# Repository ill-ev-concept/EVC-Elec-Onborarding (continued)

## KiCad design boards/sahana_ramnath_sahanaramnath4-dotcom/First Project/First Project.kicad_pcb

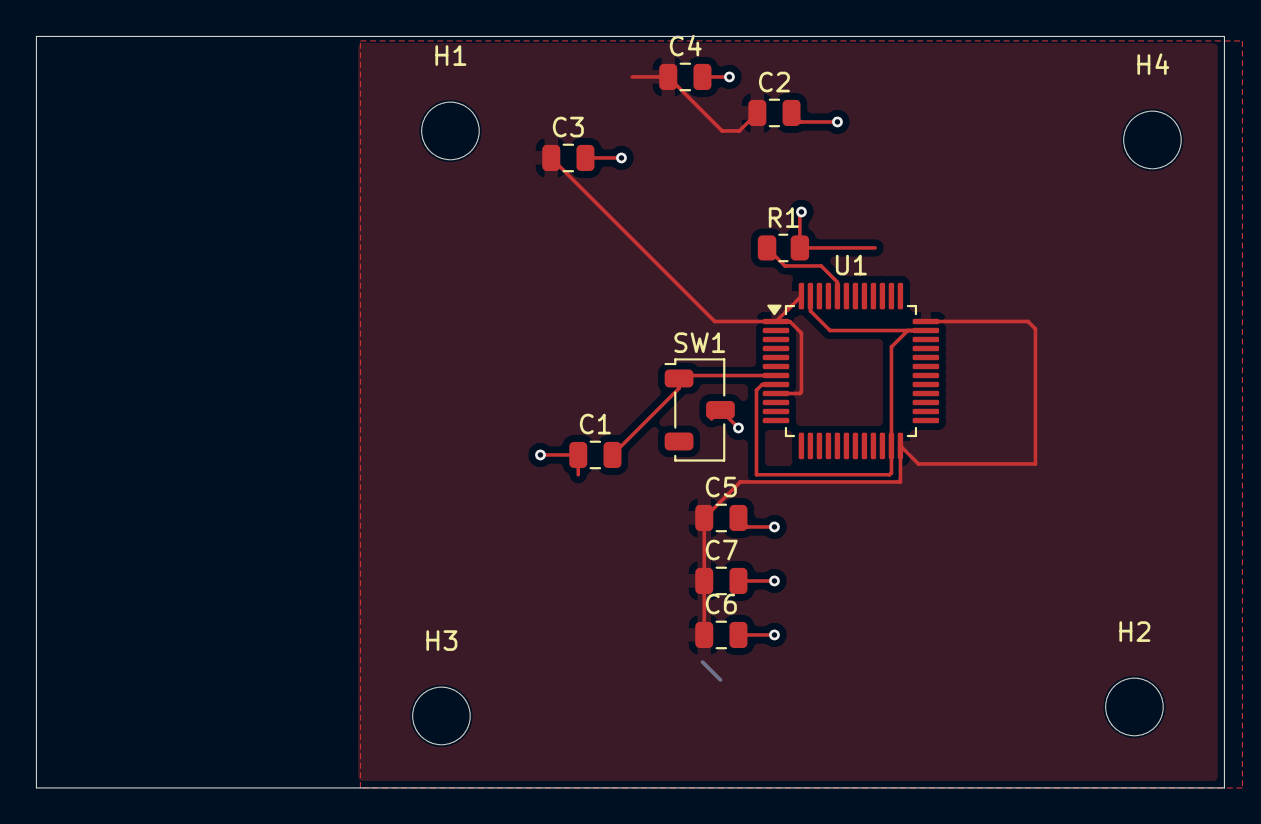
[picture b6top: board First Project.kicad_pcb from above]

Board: 2 copper layers, 66.0 x 41.8 mm, 14 parts (0 on the bottom side), 5 nets.

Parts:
C1: 100nF; C_0805_2012Metric
C2, C3, C6: 100 nF; C_0805_2012Metric
C4, C5: 100 nf; C_0805_2012Metric
C7: 4.7 microFarads; C_0805_2012Metric
H1, H2, H3, H4: MountingHole; MountingHole_3.2mm_M3
R1: 10K ohms; R_0805_2012Metric
SW1: SW_Push; Nidec_Copal_CAS-120A
U1: STM32F103C8Tx; LQFP-48_7x7mm_P0.5mm

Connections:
+3.3V: C2.1, C3.1, C4.1, C5.1, C6.1, C7.1, U1.1 (VBAT), U1.9 (VDDA), U1.24 (VDD), U1.36 (VDD), U1.48 (VDD)
BOOTOO: R1.1, U1.44 (BOOT0)
GND: C1.1, C2.2, C3.2, C4.2, C5.2, C6.2, C7.2, R1.2, SW1.2
NRST: C1.2, SW1.1, U1.7 (NRST)
unnamed: U1.8 (VSSA), U1.23 (VSS), U1.35 (VSS), U1.47 (VSS)

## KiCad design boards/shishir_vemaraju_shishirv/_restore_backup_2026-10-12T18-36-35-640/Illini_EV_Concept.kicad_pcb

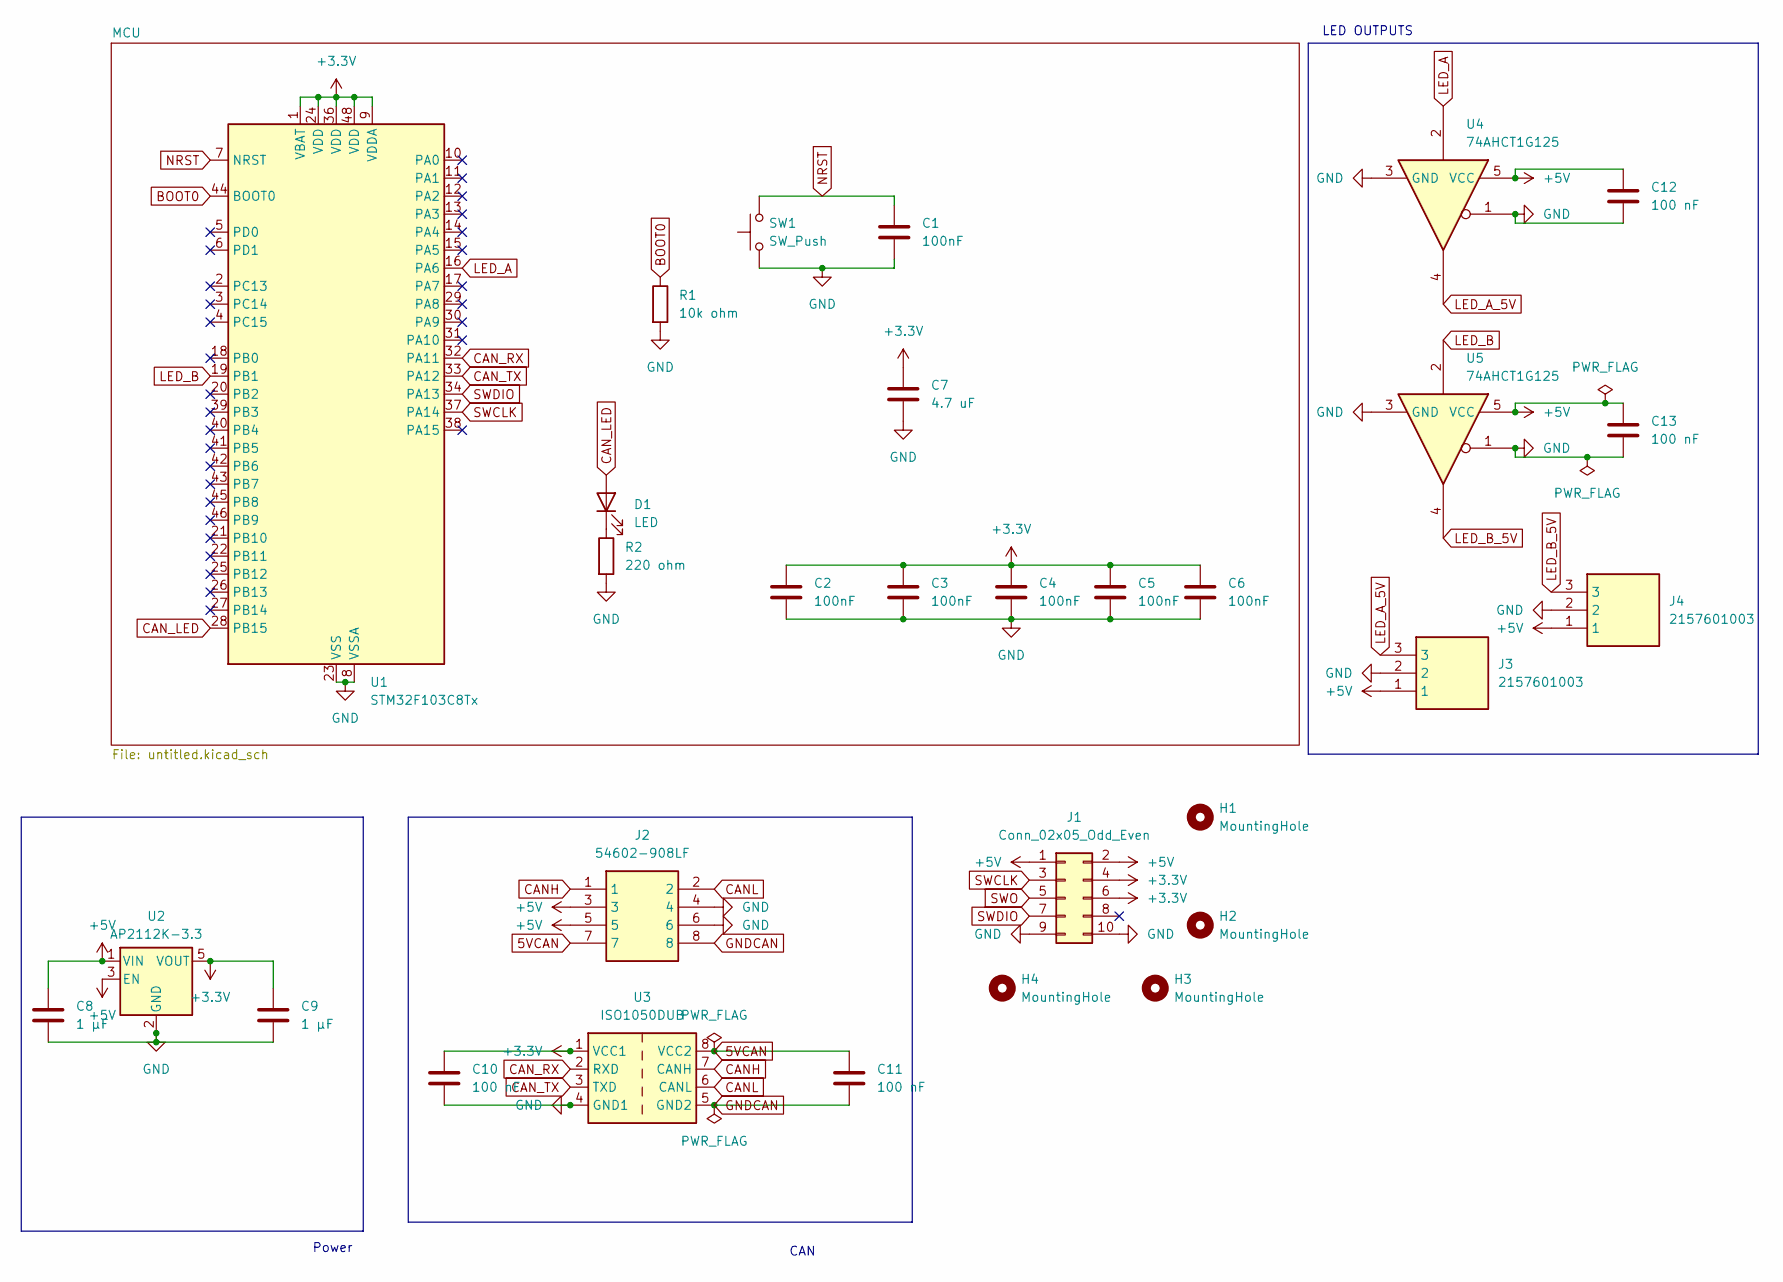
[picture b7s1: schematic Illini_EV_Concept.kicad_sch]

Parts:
C1, C2, C3, C4, C5, C6: 100nF; C_0603_1608Metric
C7: 4.7 uF; C_0603_1608Metric
C8, C9: 1 μF; C_0603_1608Metric
C10, C11, C12, C13: 100 nF; C_0603_1608Metric
D1: LED; LED_0603_1608Metric
H1, H2, H3, H4: MountingHole; MountingHole_4.3mm_M4
J1: Conn_02x05_Odd_Even; PinHeader_2x05_P2.54mm_Vertical
J2: 54602-908LF; 54602908LF; Manufacturer_Part_Number 54602-908LF
J3, J4: 2157601003; 215760YY03; Manufacturer_Part_Number 2157601003
R1: 10k ohm; R_0603_1608Metric
R2: 220 ohm; R_0603_1608Metric
SW1: SW_Push; SW_PUSH_6mm
U1: STM32F103C8Tx; LQFP-48_7x7mm_P0.5mm
U2: AP2112K-3.3; SOT-23-5
U3: ISO1050DUB; SOP-8_6.62x9.15mm_P2.54mm
U4, U5: 74AHCT1G125; SOT-23-5

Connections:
5VCAN: C11.1, J2.7, U3.8 (VCC2)
+3.3V: C2.1, C3.1, C4.1, C5.1, C6.1, C7.1, C9.1, C10.1, J1.4, J1.6, U1.1 (VBAT), U1.9 (VDDA), U1.24 (VDD), U1.36 (VDD), U1.48 (VDD), U2.5 (VOUT), U3.1 (VCC1)
+5V: C8.1, C12.1, C13.1, J1.1, J1.2, J2.3, J2.5, J3.1, J4.1, U2.1 (VIN), U2.3 (EN), U4.5 (VCC), U5.5 (VCC)
BOOT0: R1.1, U1.44 (BOOT0)
CANH: J2.1, U3.7 (CANH)
CANL: J2.2, U3.6 (CANL)
CAN_LED: D1.2 (A), U1.28 (PB15)
CAN_RX: U1.32 (PA11), U3.2 (RXD)
CAN_TX: U1.33 (PA12), U3.3 (TXD)
GND: C1.2, C2.2, C3.2, C4.2, C5.2, C6.2, C7.2, C8.2, C9.2, C10.2, C12.2, C13.2, J1.9, J1.10, J2.4, J2.6, J3.2, J4.2, R1.2, R2.2, SW1.1, U1.8 (VSSA), U1.23 (VSS), U1.35 (VSS), U1.47 (VSS), U2.2 (GND), U3.4 (GND1), U4.1, U4.3 (GND), U5.1, U5.3 (GND)
GNDCAN: C11.2, J2.8, U3.5 (GND2)
LED_A: U1.16 (PA6), U4.2
LED_A_5V: J3.3, U4.4
LED_B: U1.19 (PB1), U5.2
LED_B_5V: J4.3, U5.4
NRST: C1.1, SW1.2, U1.7 (NRST)
unnamed: D1.1 (K), R2.1
SWCLK: J1.3, U1.37 (PA14)
SWDIO: J1.7, U1.34 (PA13)
SWO: J1.5

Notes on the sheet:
Power
CAN
LED OUTPUTS

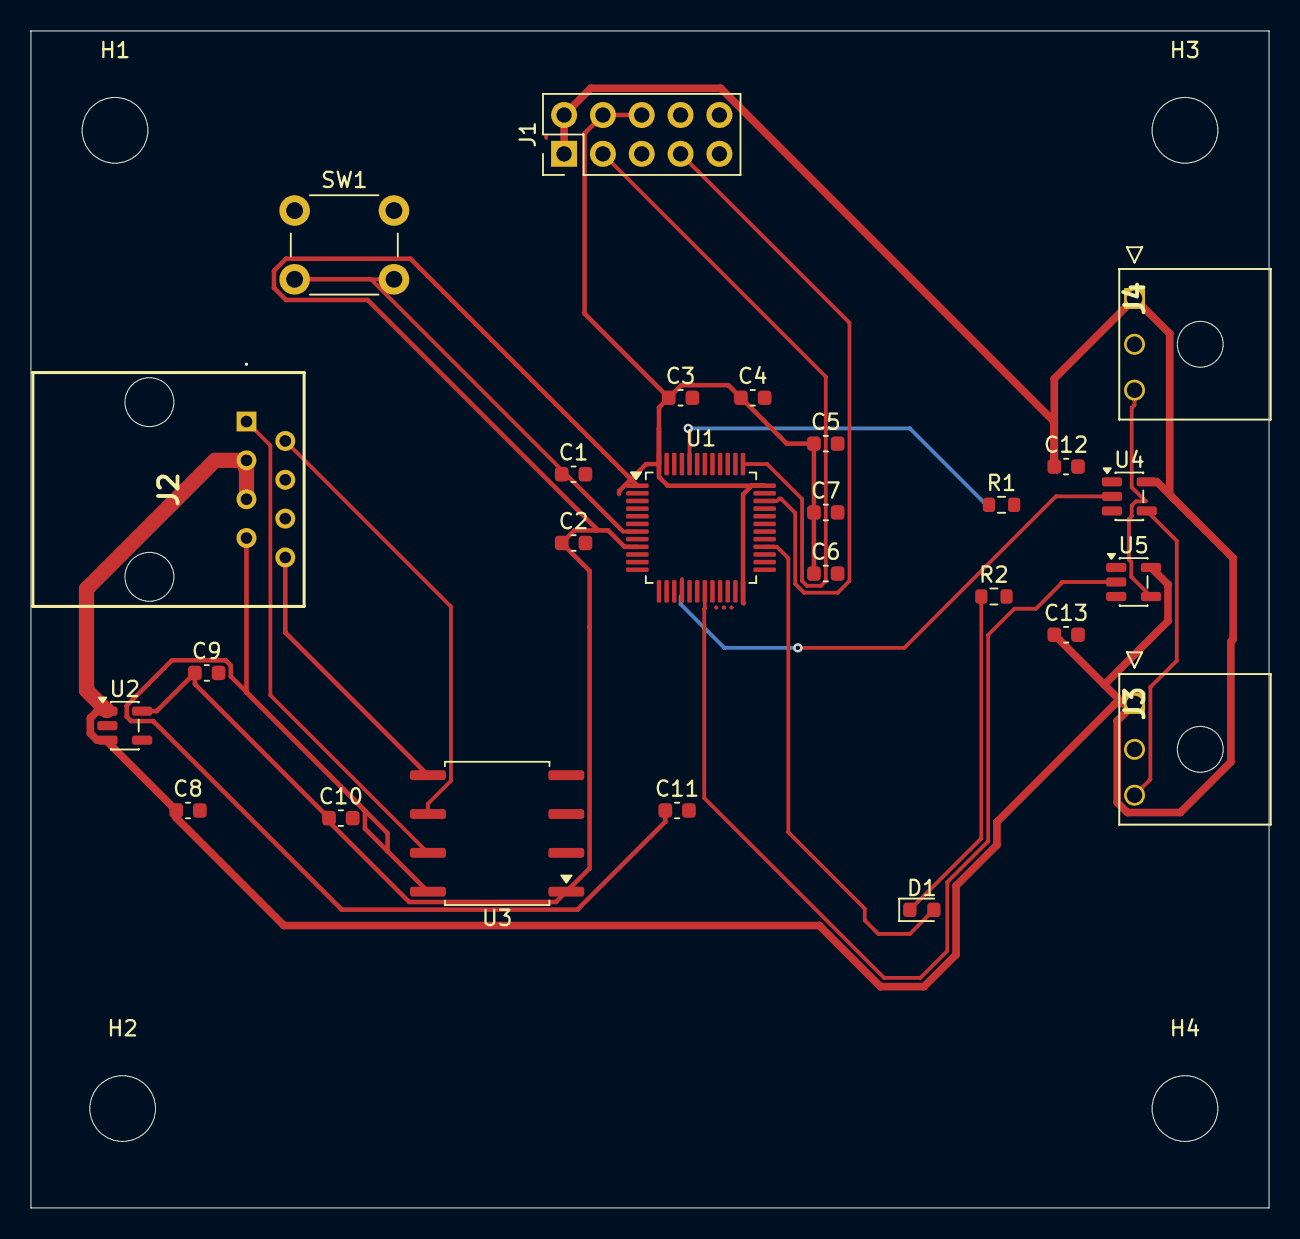
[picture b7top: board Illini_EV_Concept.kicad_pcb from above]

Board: 2 copper layers, 81.0 x 77.0 mm, 30 parts (0 on the bottom side), 19 nets.
